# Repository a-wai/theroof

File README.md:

# theroof

*theroof* is a GAL chip programmer Arduino shield, based on the
[afterburner](https://github.com/ole00/afterburner/) by *`ole00`*.

It uses a LT1301 in order to get rid of the MT3608 module, which requires
a nasty hack to be used for this project.

## Licensing

Copyright 2019, Arnaud Ferraris.

This documentation describes Open Hardware and is licensed under the
CERN OHL v.1.2.

You may redistribute and modify this documentation under the terms of the
[CERN OHL v.1.2](http://ohwr.org/cernohl). This documentation is distributed
WITHOUT ANY EXPRESS OR IMPLIED WARRANTY, INCLUDING OF MERCHANTABILITY,
SATISFACTORY QUALITY AND FITNESS FOR A PARTICULAR PURPOSE.

Please see the CERN OHL v.1.2 for applicable conditions.

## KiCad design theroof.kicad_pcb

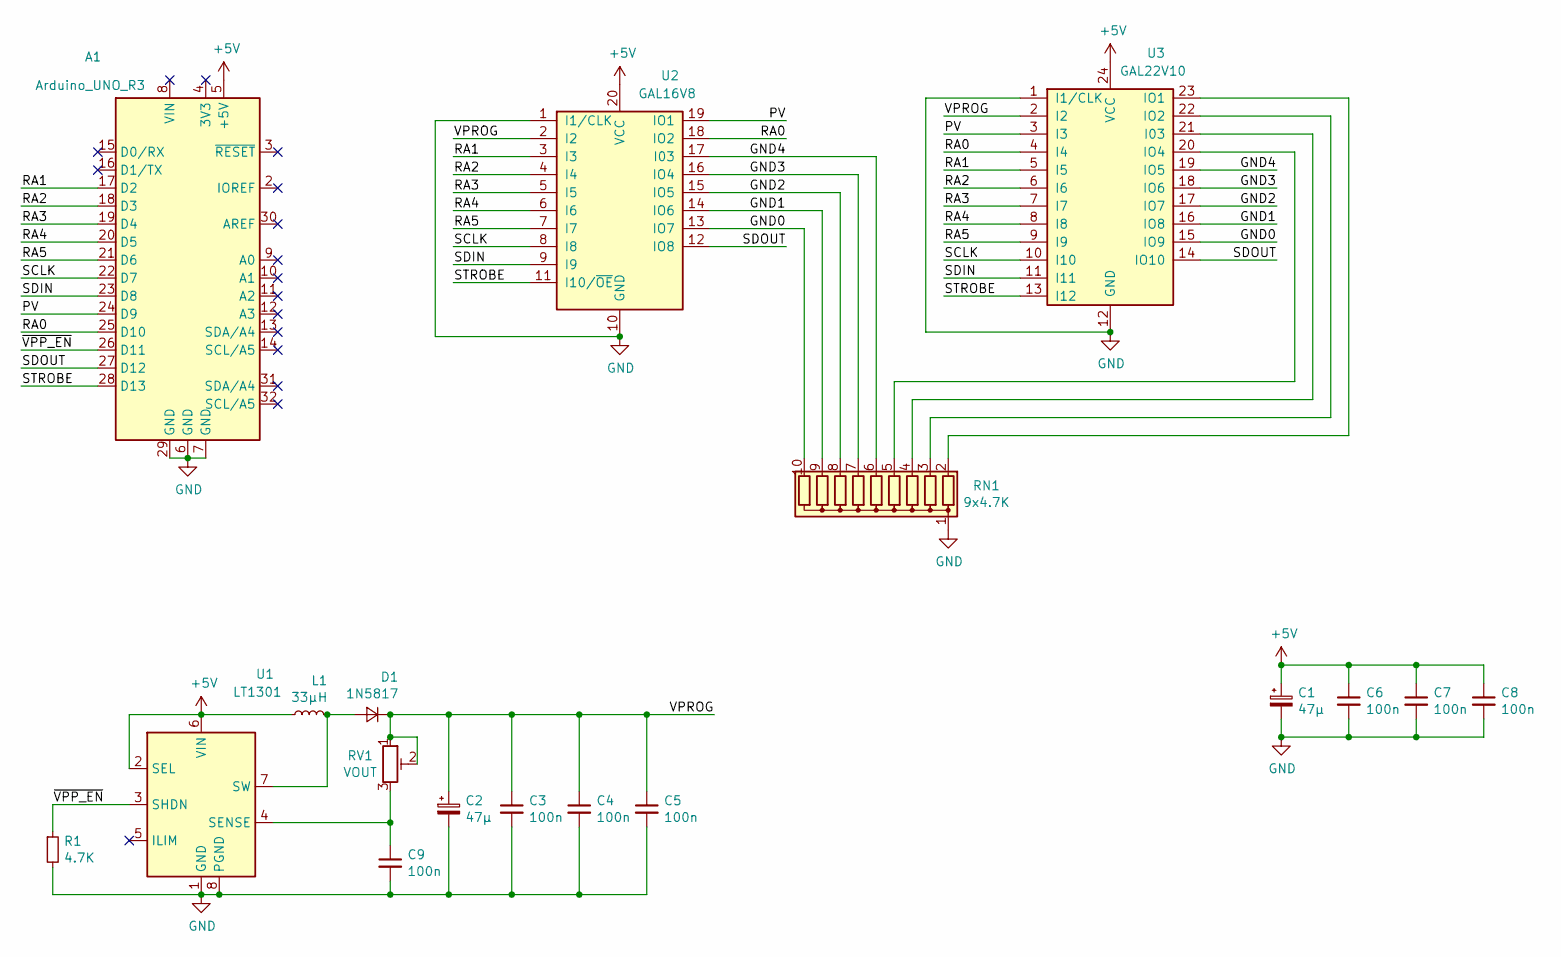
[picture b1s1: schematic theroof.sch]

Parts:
A1: Arduino_UNO_R3
C1, C2: 47µ; CP_Radial_D8.0mm_P3.80mm
C3, C4, C5, C6, C7, C8, C9: 100n; C_Disc_D3.8mm_W2.6mm_P2.50mm
D1: 1N5817; D_DO-41_SOD81_P7.62mm_Horizontal
L1: 33µH; L_Radial_D10.5mm_P4.00x5.00mm_Murata_1200RS
R1: 4.7K; R_Axial_DIN0207_L6.3mm_D2.5mm_P7.62mm_Horizontal
RN1: 9x4.7K; R_Array_SIP10
RV1: VOUT; Potentiometer_Bourns_3266X_Horizontal
U1: LT1301; DIP-8_W7.62mm_Socket_LongPads
U2: GAL16V8; DIP_Socket-20_W4.3_W5.08_W7.62_W10.16_W10.9_3M_220-3342-00-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
U3: GAL22V10; DIP_Socket-24_W4.3_W5.08_W7.62_W10.16_W10.9_3M_224-5248-00-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

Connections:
+5V: A1.5 (+5V), C1.1, C6.1, C7.1, C8.1, L1.1, U1.2 (SEL), U1.6 (VIN), U2.20 (VCC), U3.24 (VCC)
/GND0: RN1.10 (R9), U2.13 (IO7), U3.15 (IO9)
/GND1: RN1.9 (R8), U2.14 (IO6), U3.16 (IO8)
/GND2: RN1.8 (R7), U2.15 (IO5), U3.17 (IO7)
/GND3: RN1.7 (R6), U2.16 (IO4), U3.18 (IO6)
/GND4: RN1.6 (R5), U2.17 (I03), U3.19 (IO5)
/PV: A1.24 (D9), U2.19 (IO1), U3.3 (I3)
/RA0: A1.25 (D10), U2.18 (IO2), U3.4 (I4)
/RA1: A1.17 (D2), U2.3 (I3), U3.5 (I5)
/RA2: A1.18 (D3), U2.4 (I4), U3.6 (I6)
/RA3: A1.19 (D4), U2.5 (I5), U3.7 (I7)
/RA4: A1.20 (D5), U2.6 (I6), U3.8 (I8)
/RA5: A1.21 (D6), U2.7 (I7), U3.9 (I9)
/SCLK: A1.22 (D7), U2.8 (I8), U3.10 (I10)
/SDIN: A1.23 (D8), U2.9 (I9), U3.11 (I11)
/SDOUT: A1.27 (D12), U2.12 (IO8), U3.14 (IO10)
/STROBE: A1.28 (D13), U2.11 (I10/~OE~), U3.13 (I12)
/VPROG: C2.1, C3.1, C4.1, C5.1, D1.1 (K), RV1.1, RV1.2, U2.2 (I2), U3.2 (I2)
/~VPP_EN: A1.26 (D11), R1.1, U1.3 (SHDN)
GND: A1.6 (GND), A1.7 (GND), A1.29 (GND), C1.2, C2.2, C3.2, C4.2, C5.2, C6.2, C7.2, C8.2, C9.2, R1.2, RN1.1 (common), U1.1 (GND), U1.8 (PGND), U2.1 (I1/CLK), U2.10 (GND), U3.1 (I1/CLK), U3.12 (GND)
unnamed: C9.1, RV1.3, U1.4 (SENSE)
unnamed: D1.2 (A), L1.2, U1.7 (SW)
unnamed: RN1.2 (R1), U3.23 (IO1)
unnamed: RN1.3 (R2), U3.22 (IO2)
unnamed: RN1.4 (R3), U3.21 (I03)
unnamed: RN1.5 (R4), U3.20 (IO4)

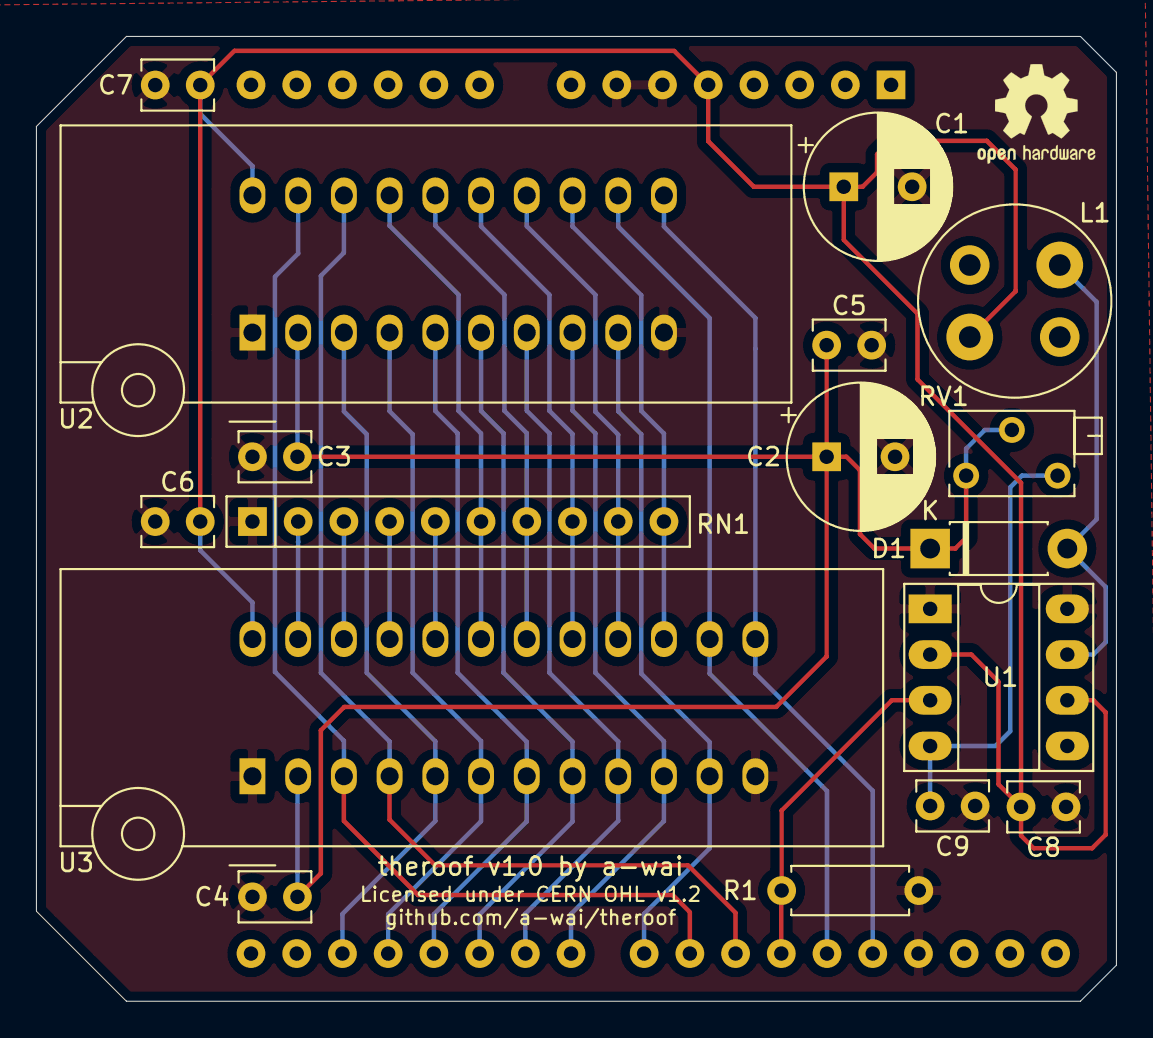
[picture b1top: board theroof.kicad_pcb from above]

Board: 2 copper layers, 60.0 x 53.6 mm, 18 parts (1 on the bottom side), 26 nets.

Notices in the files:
theroof.kicad_pcb:
Licensed under CERN OHL v1.2
